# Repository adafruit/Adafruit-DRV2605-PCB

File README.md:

# Adafruit DRV2605 Haptic Motor Controller PCB
<a href="http://www.adafruit.com/products/2305"><br/>
Click here to purchase one from the Adafruit shop</a>

The DRV2605 from TI is a fancy little motor driver. Rather than controlling a stepper motor or DC motor, its designed specifically for controlling haptic motors - buzzers and vibration motors. Normally one would just turn those kinds of motors on and off, but this driver has the ability to have various effects when driving a vibe motor. For example, ramping the vibration level up and down, 'click' effects, different buzzer levels, or even having the vibration follow a musical/audio input.

PCB files for Adafruit DRV2605 Haptic Motor Driver. The format is EagleCAD schematic and board layout
- https://www.adafruit.com/product/2305

### License

Adafruit invests time and resources providing this open source design, please support Adafruit and open-source hardware by purchasing products from [Adafruit](https://www.adafruit.com)!

All text above must be included in any redistribution

Designed by Limor Fried/Ladyada for Adafruit Industries.
Creative Commons Attribution/Share-Alike, all text above must be included in any redistribution. 
See license.txt for additional information.

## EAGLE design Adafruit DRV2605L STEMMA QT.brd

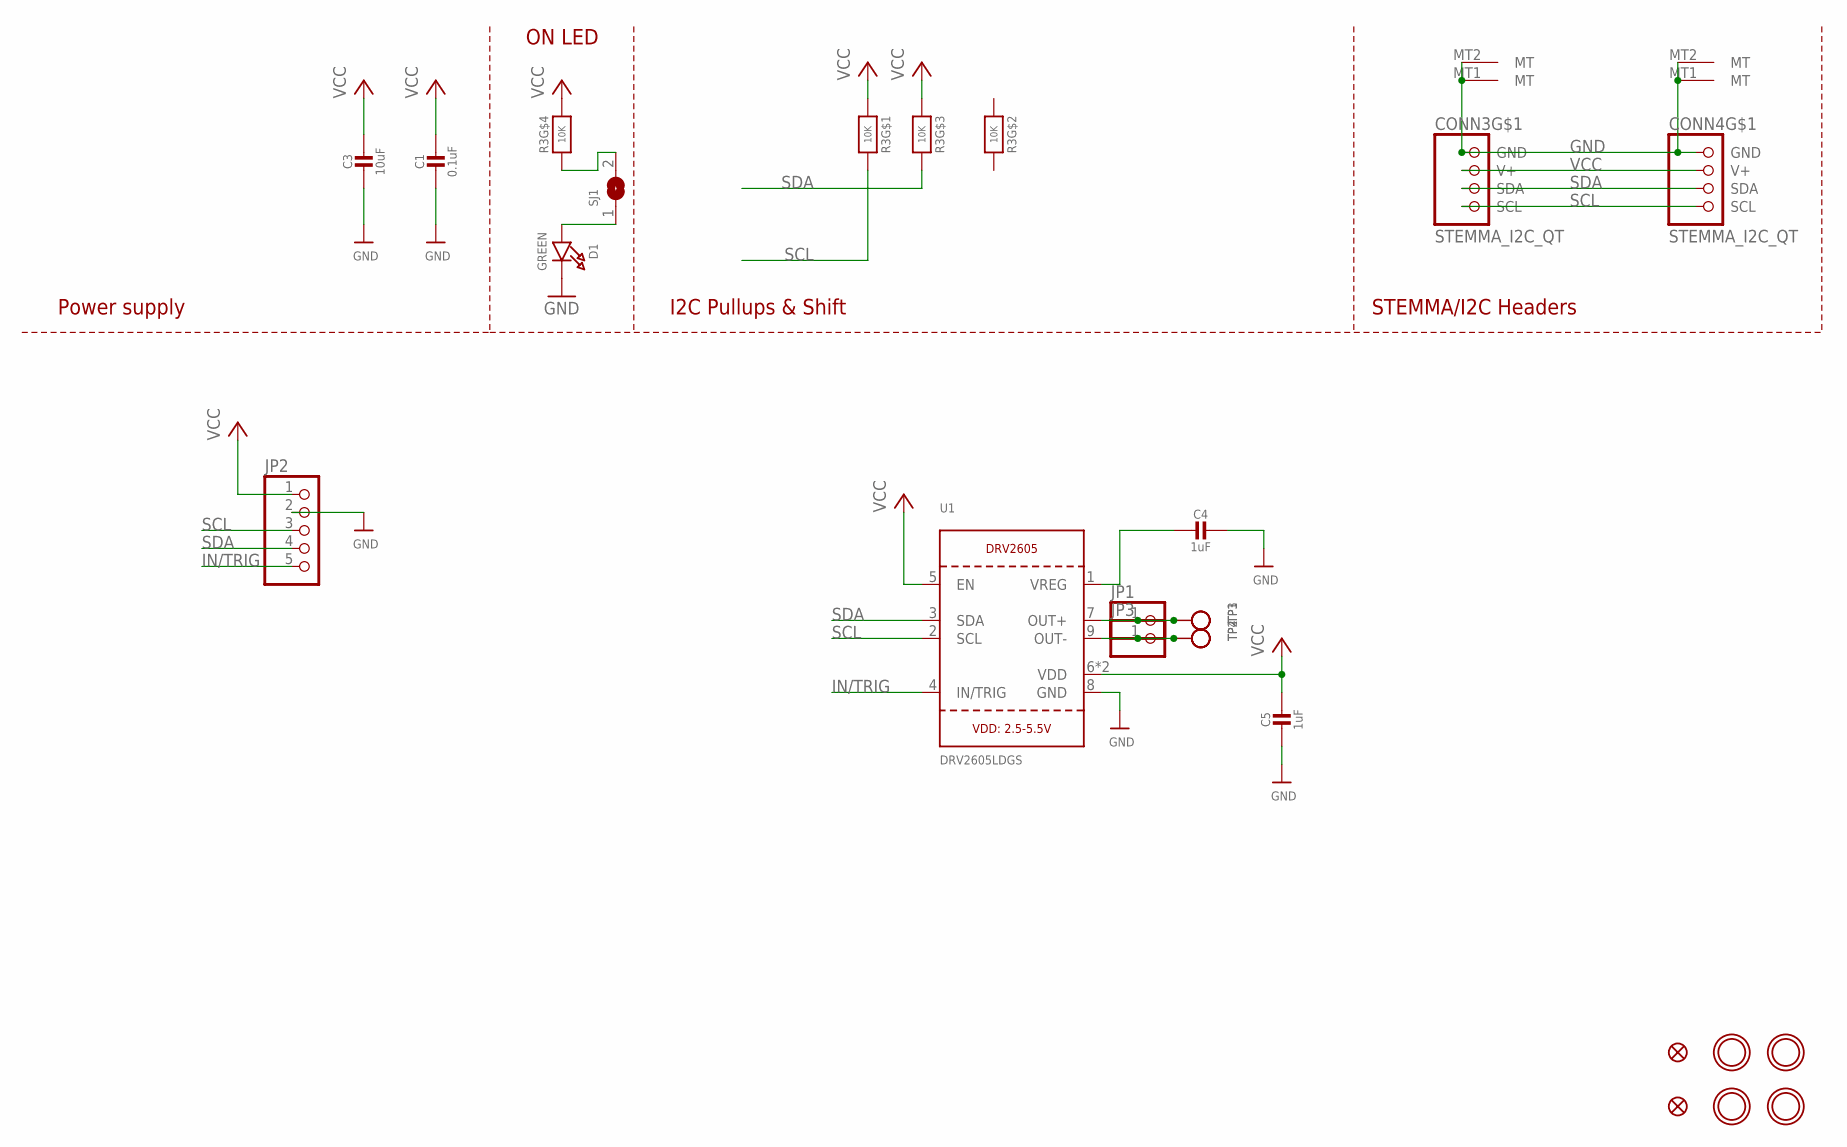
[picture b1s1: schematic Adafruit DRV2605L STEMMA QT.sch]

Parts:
C1: 0.1uF; 0603-NO
C3: 10uF; 0805-NO
C4, C5: 1uF; 0603-NO
CONN3, CONN4: STEMMA_I2C_QT; JST_SH4
D1: GREEN; CHIPLED_0603_NOOUTLINE
FID3, FID4: FIDUCIAL_1MM
JP1, JP3: HEADER-1X1; 1X01_OVAL
JP2: HEADER-1X576MIL; 1X05_ROUND_76
R3: 10K; RESPACK_4X0603
SJ1: SOLDERJUMPERCLOSED; SOLDERJUMPER_CLOSEDWIRE
TP1, TP2, TP3, TP4: TESTPOINTPAD2MM; TESTPOINT_PAD_2MM
U1: DRV2605LDGS; PSOP10
U$1, U$17, U$19, U$21: MOUNTINGHOLE2.5; MOUNTINGHOLE_2.5_PLATED

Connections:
GND: C1.2, C3.2, C4.1, C5.2, CONN3.1 (GND), CONN3.MT1 (MT), CONN3.MT2 (MT), CONN4.1 (GND), CONN4.MT1 (MT), CONN4.MT2 (MT), D1.C, JP2.2, U1.8 (GND)
IN/TRIG: JP2.5, U1.4 (IN/TRIG)
unnamed: R3.4 (1), SJ1.2
unnamed: D1.A, SJ1.1
unnamed: C4.2, U1.1 (VREG)
OUT+: JP1.1, TP1.P$1, TP3.P$1, U1.7 (OUT+)
OUT-: JP3.1, TP2.P$1, TP4.P$1, U1.9 (OUT-)
SCL: CONN3.4 (SCL), CONN4.4 (SCL), JP2.3, R3.8 (2), U1.2 (SCL)
SDA: CONN3.3 (SDA), CONN4.3 (SDA), JP2.4, R3.6 (2), U1.3 (SDA)
VCC: C1.1, C3.1, C5.1, CONN3.2 (V+), CONN4.2 (V+), JP2.1, R3.1, R3.3 (1), R3.5 (2), U1.5 (EN), U1.6 (VDD), U1.10 (VDD)

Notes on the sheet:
I2C Pullups & Shift
STEMMA/I2C Headers
ON LED
Power supply

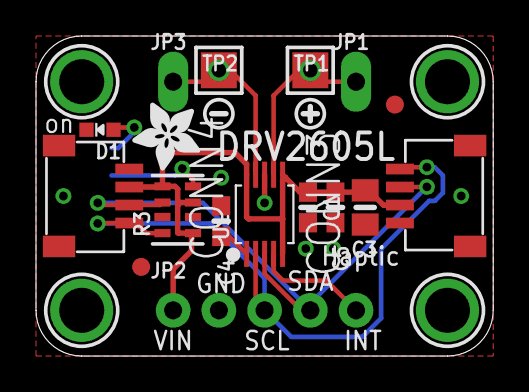
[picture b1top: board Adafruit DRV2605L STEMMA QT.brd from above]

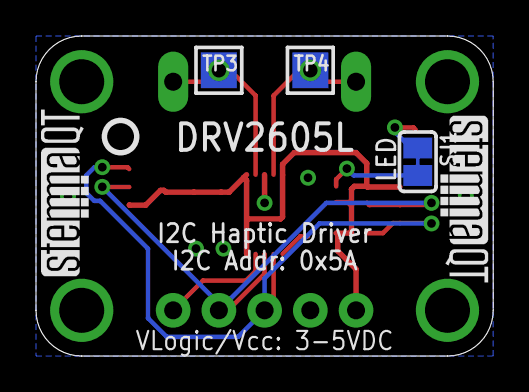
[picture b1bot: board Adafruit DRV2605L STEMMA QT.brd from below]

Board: 2 copper layers, 25.4 x 17.8 mm, 29 parts (6 on the bottom side), 10 nets.

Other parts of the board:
U$2: SYMBOL_PLUS
U$3: SYMBOL_MINUS
U$22: ADAFRUIT_3.5MM
U$25: PCBFEAT-REV-040
U$30, U$31: STEMMAQT

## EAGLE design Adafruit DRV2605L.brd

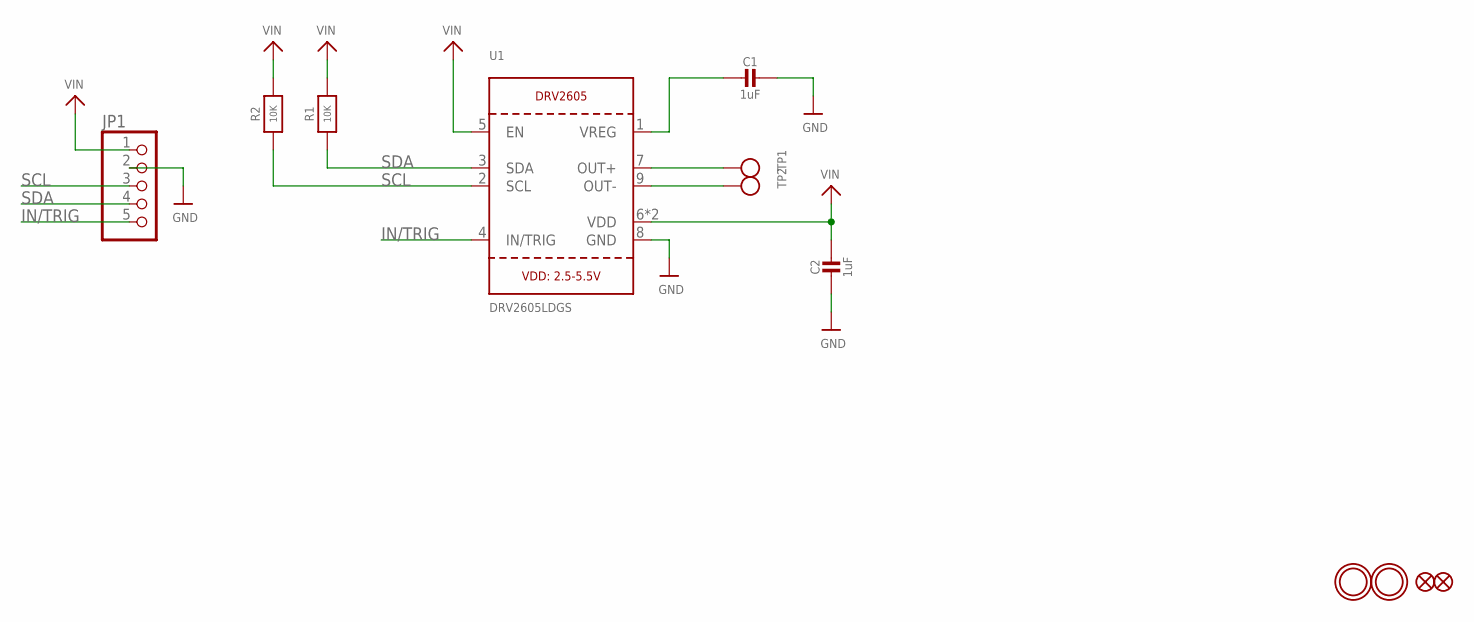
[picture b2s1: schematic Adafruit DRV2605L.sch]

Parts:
C1, C2: 1uF; 0805-NO
FID1, FID2: FIDUCIAL""; FIDUCIAL_1MM
JP1: HEADER-1X576MIL_FULL; 1X05_ROUND_FULL_76
R1, R2: 10K; 0805-NO
TP1, TP2: TESTPOINTPAD2MM; TESTPOINT_PAD_2MM
U1: DRV2605LDGS; PSOP10
U$2, U$3: MOUNTINGHOLE2.5; MOUNTINGHOLE_2.5_PLATED

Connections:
GND: C1.1, C2.2, JP1.2, U1.8 (GND)
IN/TRIG: JP1.5, U1.4 (IN/TRIG)
unnamed: C1.2, U1.1 (VREG)
OUT+: TP1.P$1, U1.7 (OUT+)
OUT-: TP2.P$1, U1.9 (OUT-)
SCL: JP1.3, R2.1, U1.2 (SCL)
SDA: JP1.4, R1.1, U1.3 (SDA)
VIN: C2.1, JP1.1, R1.2, R2.2, U1.5 (EN), U1.6 (VDD), U1.10 (VDD)

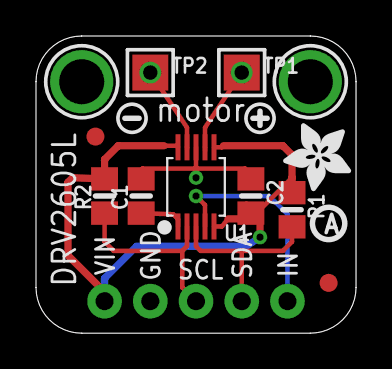
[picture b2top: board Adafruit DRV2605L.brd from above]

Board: 2 copper layers, 17.8 x 16.5 mm, 16 parts (0 on the bottom side), 8 nets.

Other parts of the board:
U$4: SYMBOL_PLUS
U$5: SYMBOL_MINUS
U$15: PCBFEAT-REV-040
U$18: ADAFRUIT_3.5MM

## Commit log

2015-03-26 init
2022-07-21 Updating image and adding STEMMA QT PCB files

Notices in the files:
parts and their libraries:
microbuilder: This work is placed in the public domain, and may be freely used for commercial and non-commercial work with the following conditions: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
